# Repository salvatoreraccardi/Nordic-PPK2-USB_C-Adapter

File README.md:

# Nordic-PPK2-USB_C-Adapter
USB-C adapter for [Nordic's Power Profiler Kit II](https://www.nordicsemi.com/Products/Development-hardware/Power-Profiler-Kit-2). Ideal for easily measuring the current drawn by a device/board.

## Enclosure
The enclosure can be printed using regular PLA. An infill of 100% is recommended.

After mounting the PCB in the enclosure, use a hot flat object (e.g. an iron) to melt the plastic 'pins'. This will lock the PCB in place.

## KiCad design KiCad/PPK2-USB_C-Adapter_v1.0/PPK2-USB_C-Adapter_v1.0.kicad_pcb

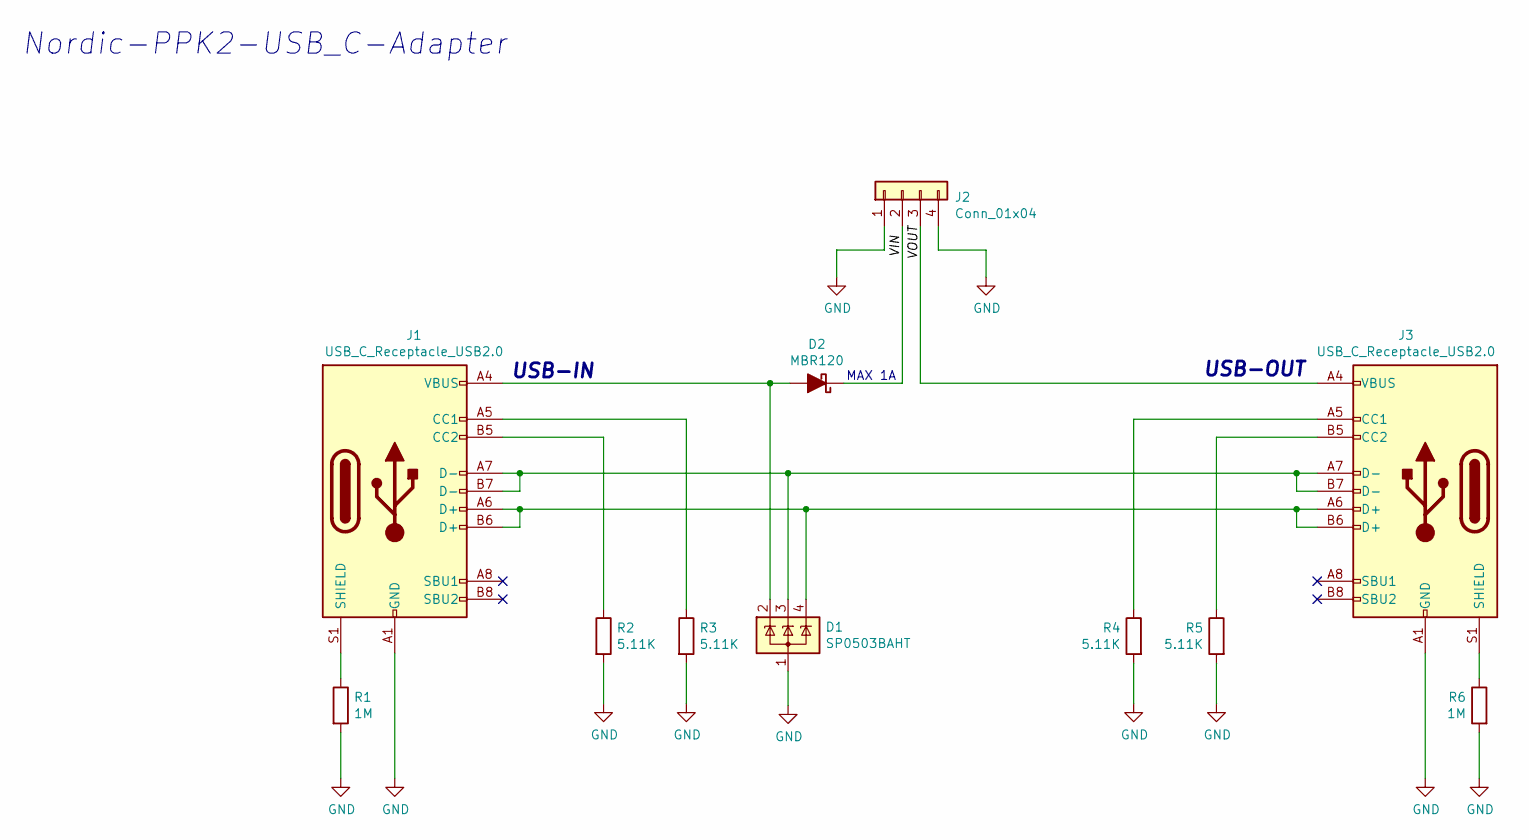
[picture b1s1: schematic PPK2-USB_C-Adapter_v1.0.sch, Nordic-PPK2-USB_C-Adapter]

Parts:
D1: SP0503BAHT; SOT-143
D2: MBR120; D_SOD-123
J1, J3: USB_C_Receptacle_USB2.0; USB_C_Receptacle_Palconn_UTC16-G
J2: Conn_01x04; PinHeader_1x04_P2.54mm_Vertical
R1, R6: 1M; R_0402_1005Metric
R2, R3, R4, R5: 5.11K; R_0402_1005Metric

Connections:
/VIN: D2.1 (K), J2.2
/VOUT: J2.3, J3.A4 (VBUS), J3.A9 (VBUS), J3.B4 (VBUS), J3.B9 (VBUS)
GND: D1.1 (A), J1.A1 (GND), J1.A12 (GND), J1.B1 (GND), J1.B12 (GND), J2.1, J2.4, J3.A1 (GND), J3.A12 (GND), J3.B1 (GND), J3.B12 (GND), R1.2, R2.2, R3.2, R4.2, R5.2, R6.2
unnamed: D1.2 (K), D2.2 (A), J1.A4 (VBUS), J1.A9 (VBUS), J1.B4 (VBUS), J1.B9 (VBUS)
unnamed: D1.3 (K), J1.A7 (D-), J1.B7 (D-), J3.A7 (D-), J3.B7 (D-)
unnamed: D1.4 (K), J1.A6 (D+), J1.B6 (D+), J3.A6 (D+), J3.B6 (D+)
unnamed: J1.A5 (CC1), R3.1
unnamed: J1.B5 (CC2), R2.1
unnamed: J1.S1 (SHIELD), R1.1
unnamed: J3.A5 (CC1), R4.1
unnamed: J3.B5 (CC2), R5.1
unnamed: J3.S1 (SHIELD), R6.1

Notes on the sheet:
USB-IN
USB-OUT
MAX 1A
Nordic-PPK2-USB_C-Adapter

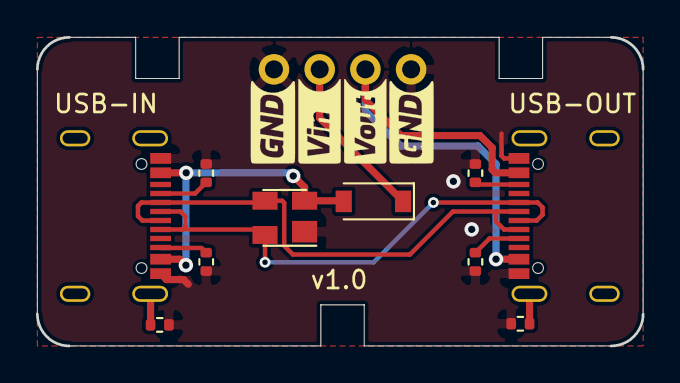
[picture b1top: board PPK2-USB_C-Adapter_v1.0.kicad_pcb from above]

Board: 2 copper layers, 33.7 x 17.1 mm, 11 parts (0 on the bottom side), 12 nets.

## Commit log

2021-10-03 last update - gerber
2021-10-06 updated silkscreen
2022-02-25 Add enclosure.
2022-03-08 Bye, .DS_Store
